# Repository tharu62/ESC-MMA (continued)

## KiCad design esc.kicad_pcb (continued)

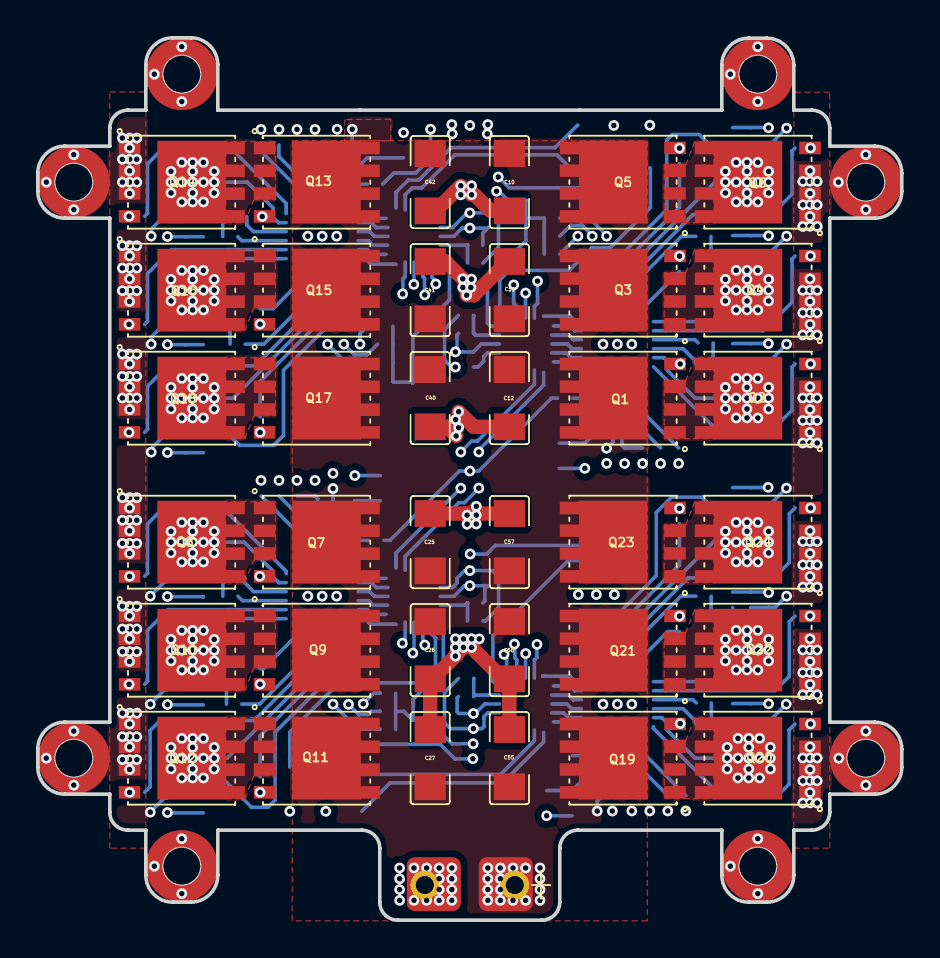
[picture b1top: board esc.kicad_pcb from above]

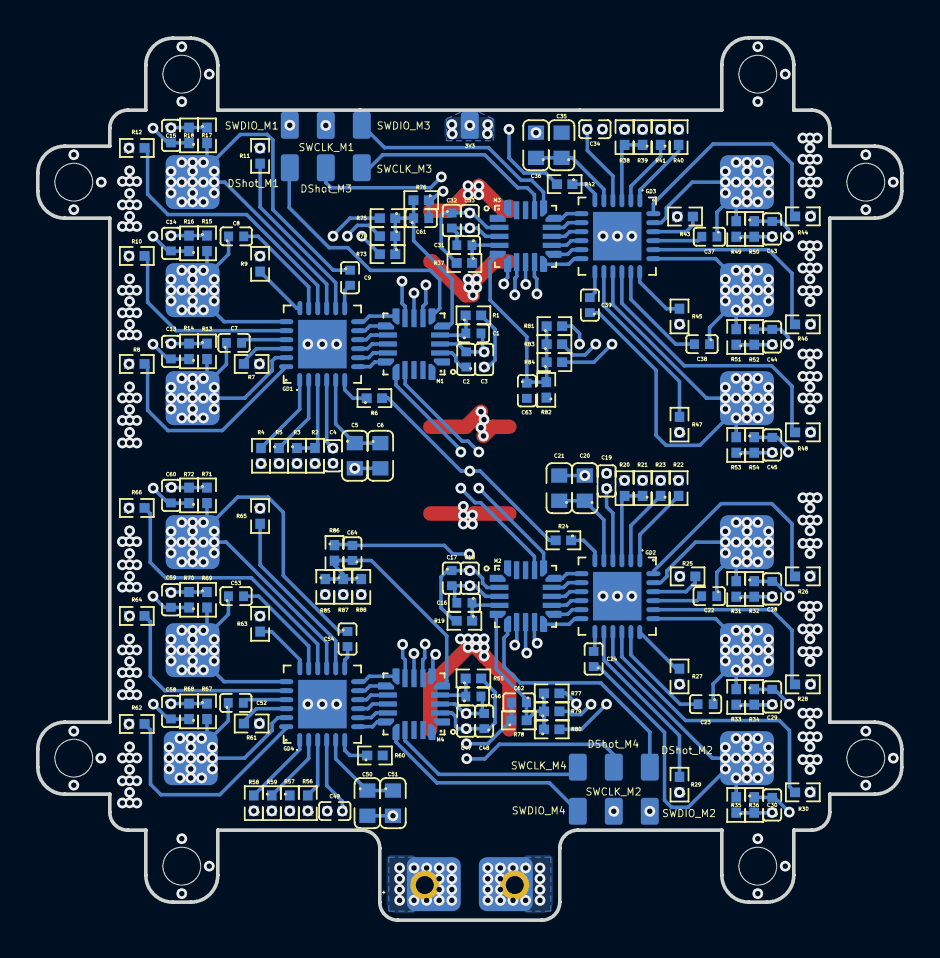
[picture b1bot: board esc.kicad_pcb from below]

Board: 4 copper layers, 48.0 x 49.0 mm, 212 parts (174 on the bottom side), 121 nets.

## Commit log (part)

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2026-05-26 ESC_V1.0
2026-05-26 edited symbols
2026-05-28 ESC_V1.1
2026-06-09 complete change in architecture,work in progress
2026-06-25 change in architecture with horizonatal half bridge
